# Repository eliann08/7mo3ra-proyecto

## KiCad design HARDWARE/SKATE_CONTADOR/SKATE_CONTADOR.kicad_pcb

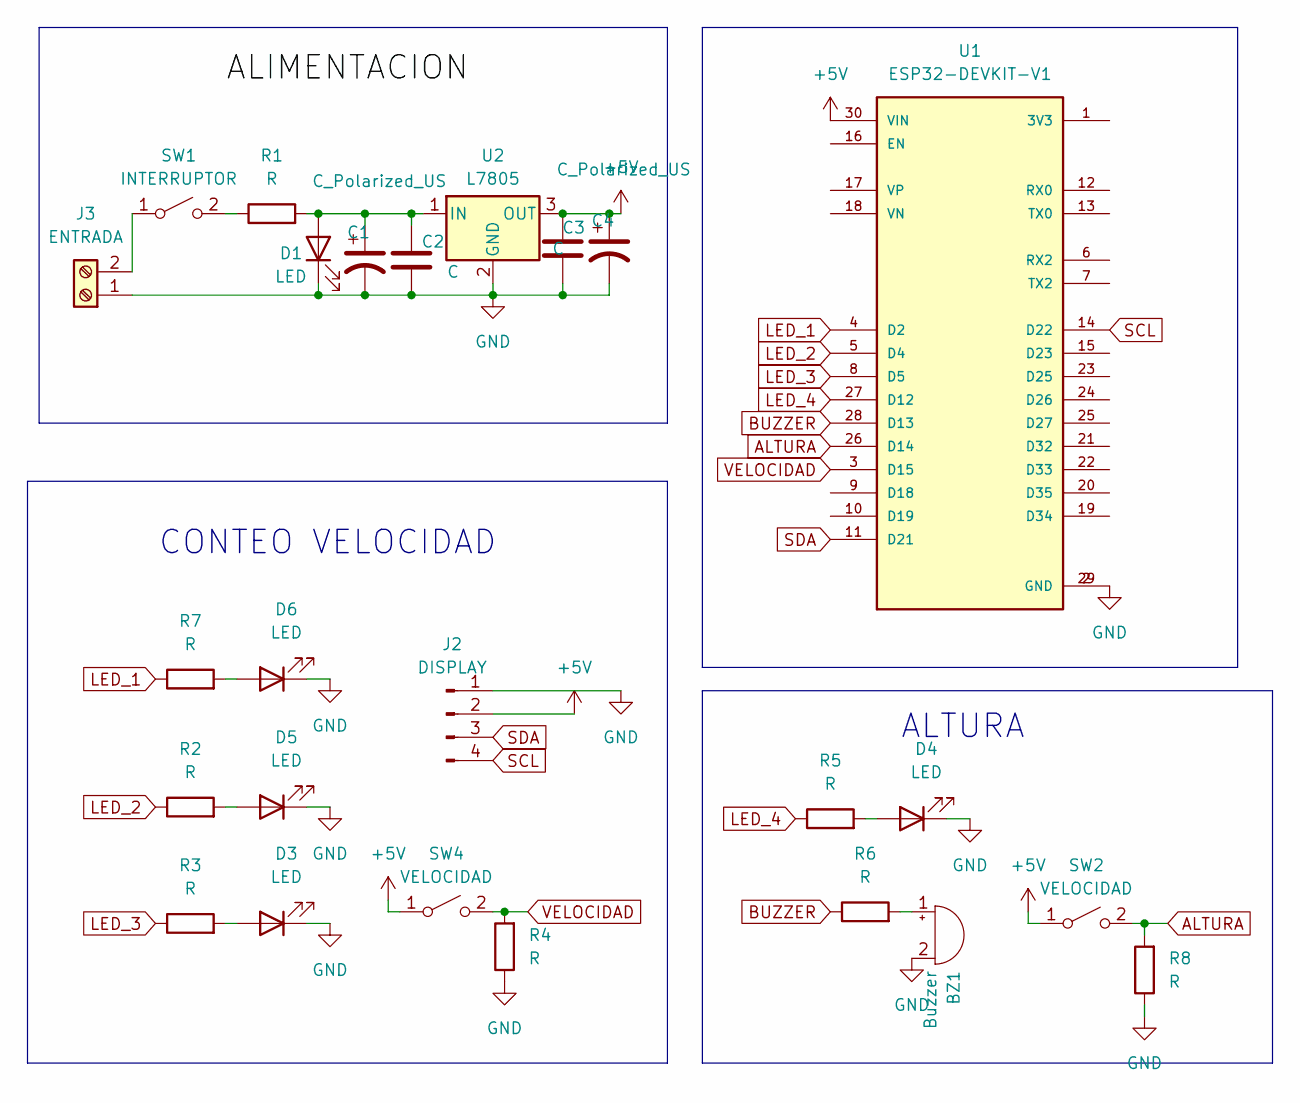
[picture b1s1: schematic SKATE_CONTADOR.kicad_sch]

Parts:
BZ1: Buzzer; PinHeader_1x02_P2.54mm_Vertical
C1, C4: C_Polarized_US; CP_Radial_D8.0mm_P5.00mm
C2, C3: C; C_Disc_D8.0mm_W2.5mm_P5.00mm
D1, D3, D4, D5, D6: LED; PinHeader_1x02_P2.54mm_Vertical
J2: DISPLAY; PinHeader_1x04_P2.54mm_Vertical
J3: ENTRADA; TerminalBlock_bornier-2_P5.08mm
R1, R2, R3, R4, R5, R6, R7, R8: R; R_0805_2012Metric_Pad1.20x1.40mm_HandSolder
SW1: INTERRUPTOR; SW_Slide_SPDT_Angled_CK_OS102011MA1Q
SW2, SW4: VELOCIDAD; SW_Tactile_Straight_KSL0Axx1LFTR
U1: ESP32-DEVKIT-V1; MODULE_ESP32_DEVKIT_V1; PARTREV N/A
U2: L7805; TO254P1011X419X2286-3

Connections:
+5V: C3.1, C4.1, J2.2, SW2.1 (A), SW4.1 (A), U1.30 (VIN), U2.3 (OUT)
ALTURA: R8.2, SW2.2 (B), U1.26 (D14)
BUZZER: R6.1, U1.28 (D13)
GND: BZ1.2 (-), C1.2, C2.2, C3.2, C4.2, D1.1 (K), D3.1 (K), D4.1 (K), D5.1 (K), D6.1 (K), J2.1, J3.1, R4.1, R8.1, U1.2 (GND), U1.29 (GND), U2.2 (GND)
LED_1: R7.1, U1.4 (D2)
LED_2: R2.1, U1.5 (D4)
LED_3: R3.1, U1.8 (D5)
LED_4: R5.1, U1.27 (D12)
unnamed: BZ1.1 (+), R6.2
unnamed: C1.1, C2.1, D1.2 (A), R1.2, U2.1 (IN)
unnamed: D3.2 (A), R3.2
unnamed: D4.2 (A), R5.2
unnamed: D5.2 (A), R2.2
unnamed: D6.2 (A), R7.2
unnamed: J3.2, SW1.1 (A)
unnamed: R1.1, SW1.2 (B)
SCL: J2.4, U1.14 (D22)
SDA: J2.3, U1.11 (D21)
VELOCIDAD: R4.2, SW4.2 (B), U1.3 (D15)

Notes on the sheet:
CONTEO VELOCIDAD
ALTURA

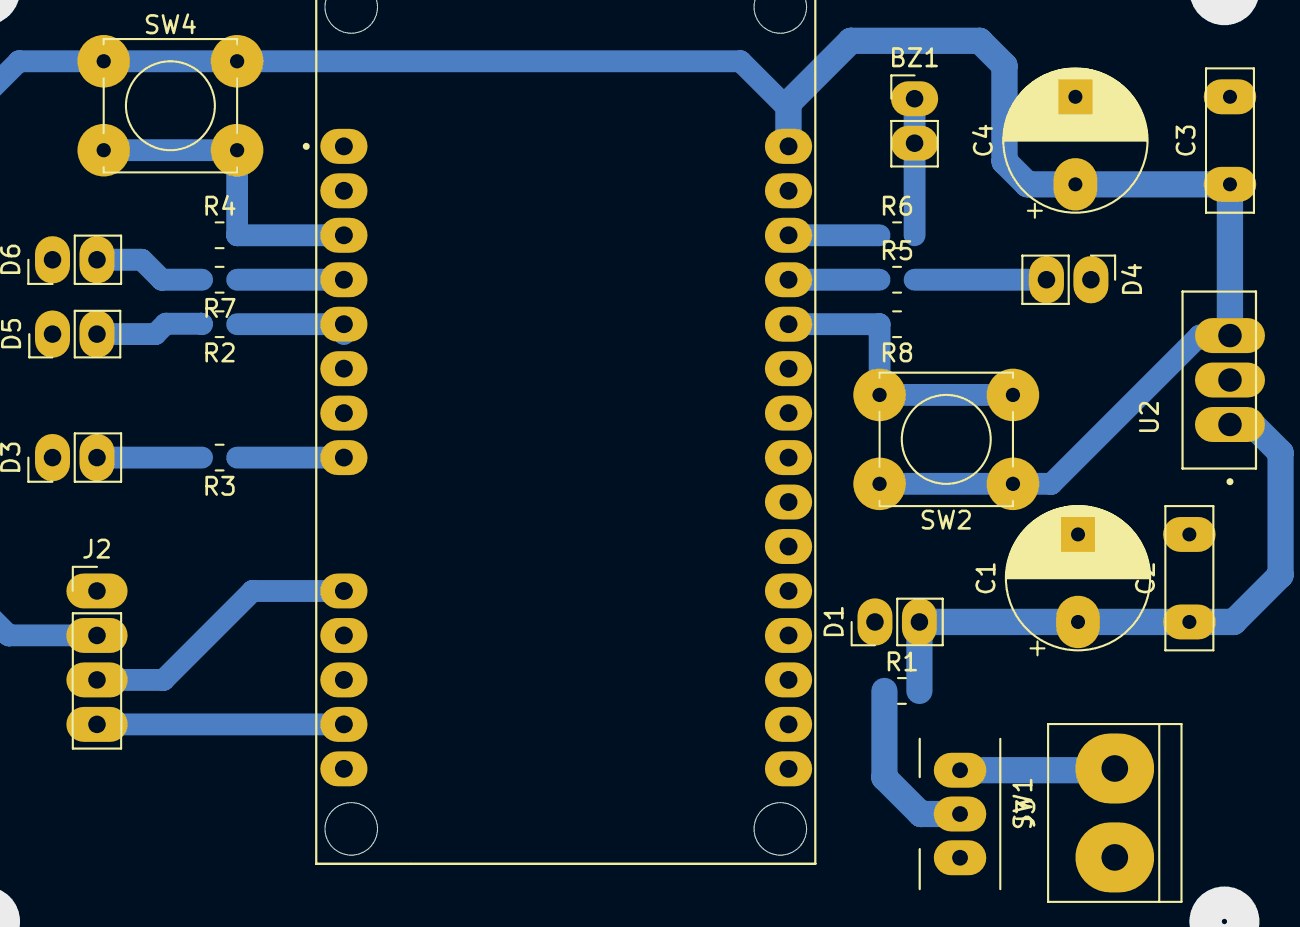
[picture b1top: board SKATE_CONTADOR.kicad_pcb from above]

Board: 2 copper layers, 25 parts (0 on the bottom side), 19 nets.

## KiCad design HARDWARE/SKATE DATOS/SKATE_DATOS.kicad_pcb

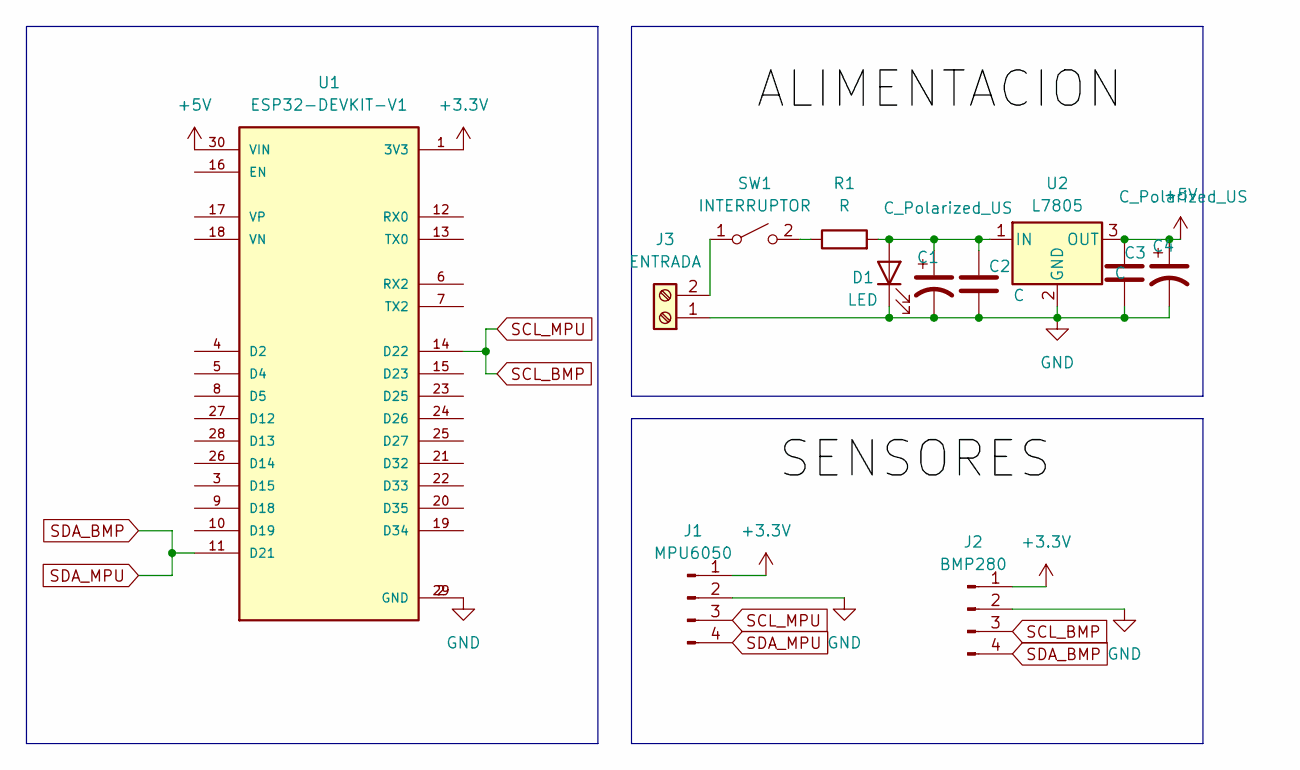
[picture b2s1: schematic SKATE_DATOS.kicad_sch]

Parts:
C1, C4: C_Polarized_US; CP_Radial_D8.0mm_P5.00mm
C2, C3: C; C_Disc_D8.0mm_W2.5mm_P5.00mm
D1: LED; LED_D5.0mm
J1: MPU6050; PinHeader_1x04_P2.54mm_Vertical
J2: BMP280; PinHeader_1x04_P2.54mm_Vertical
J3: ENTRADA; TerminalBlock_bornier-2_P5.08mm
R1: R; R_0805_2012Metric_Pad1.20x1.40mm_HandSolder
SW1: INTERRUPTOR; SW_Slide_SPDT_Angled_CK_OS102011MA1Q
U1: ESP32-DEVKIT-V1; MODULE_ESP32_DEVKIT_V1; PARTREV N/A
U2: L7805; TO254P1011X419X2286-3

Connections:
+3.3V: J1.1, J2.1, U1.1 (3V3)
+5V: C3.1, C4.1, U1.30 (VIN), U2.3 (OUT)
GND: C1.2, C2.2, C3.2, C4.2, D1.1 (K), J1.2, J2.2, J3.1, U1.2 (GND), U1.29 (GND), U2.2 (GND)
unnamed: C1.1, C2.1, D1.2 (A), R1.2, U2.1 (IN)
unnamed: J3.2, SW1.1 (A)
unnamed: R1.1, SW1.2 (B)
SCL_BMP: J1.3, J2.3, U1.14 (D22)
SDA_BMP: J1.4, J2.4, U1.11 (D21)

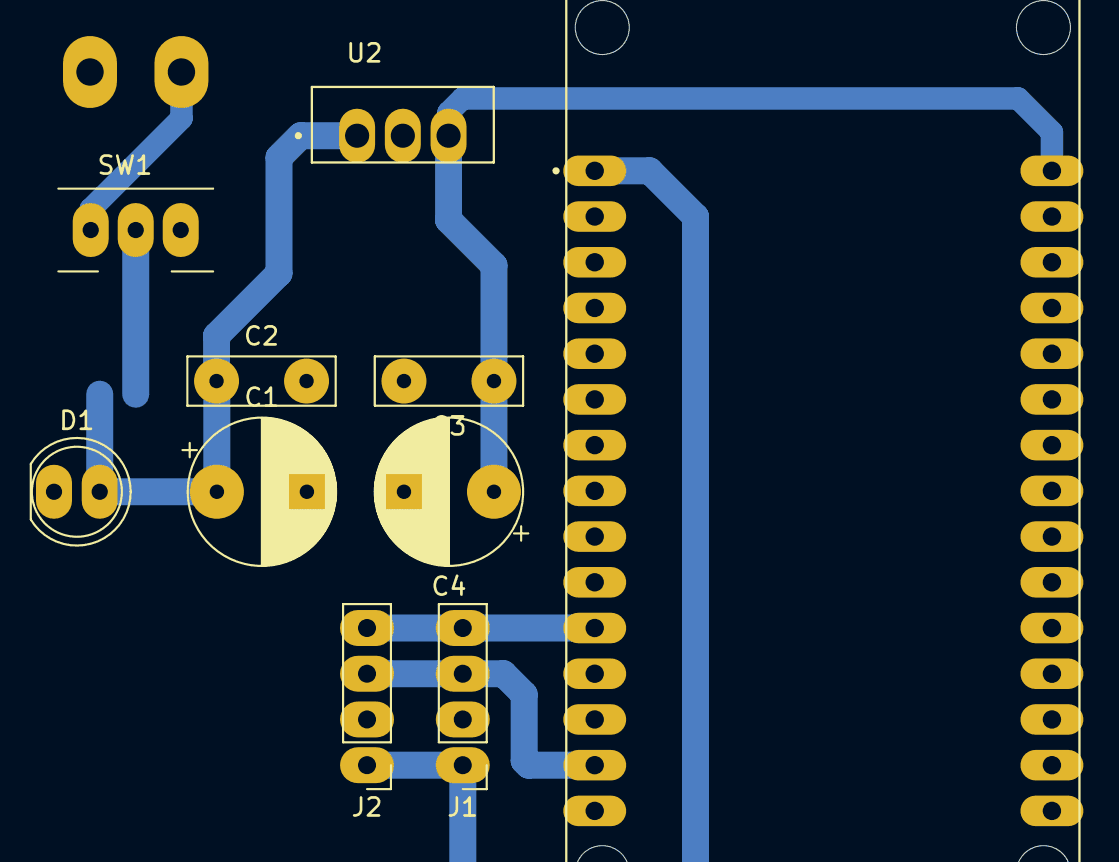
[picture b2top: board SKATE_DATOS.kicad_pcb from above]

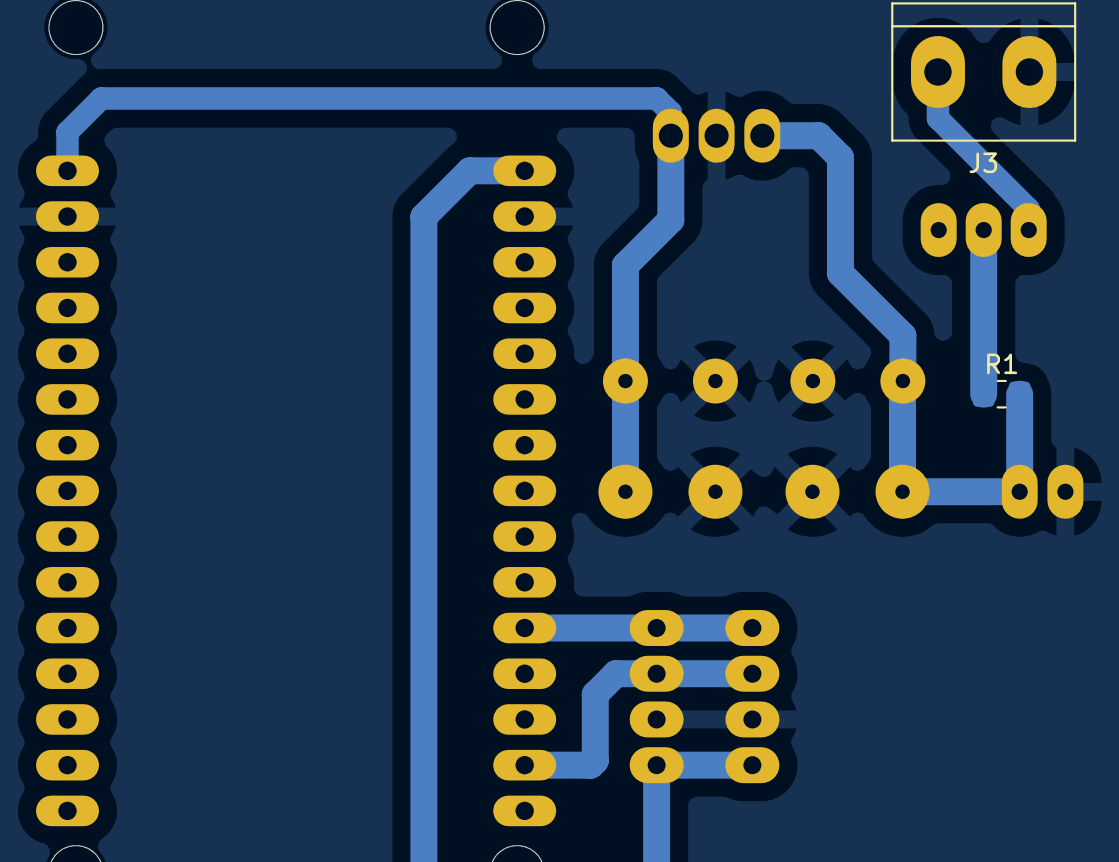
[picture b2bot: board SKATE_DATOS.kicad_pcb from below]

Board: 2 copper layers, 12 parts (2 on the bottom side), 8 nets.

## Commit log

2026-05-14 kicad
2026-05-14 3D y SOFTWARE
2026-06-04 PCB DE DATOS
2026-06-04 capacitores de filtro
2026-06-04 pines arreglados
